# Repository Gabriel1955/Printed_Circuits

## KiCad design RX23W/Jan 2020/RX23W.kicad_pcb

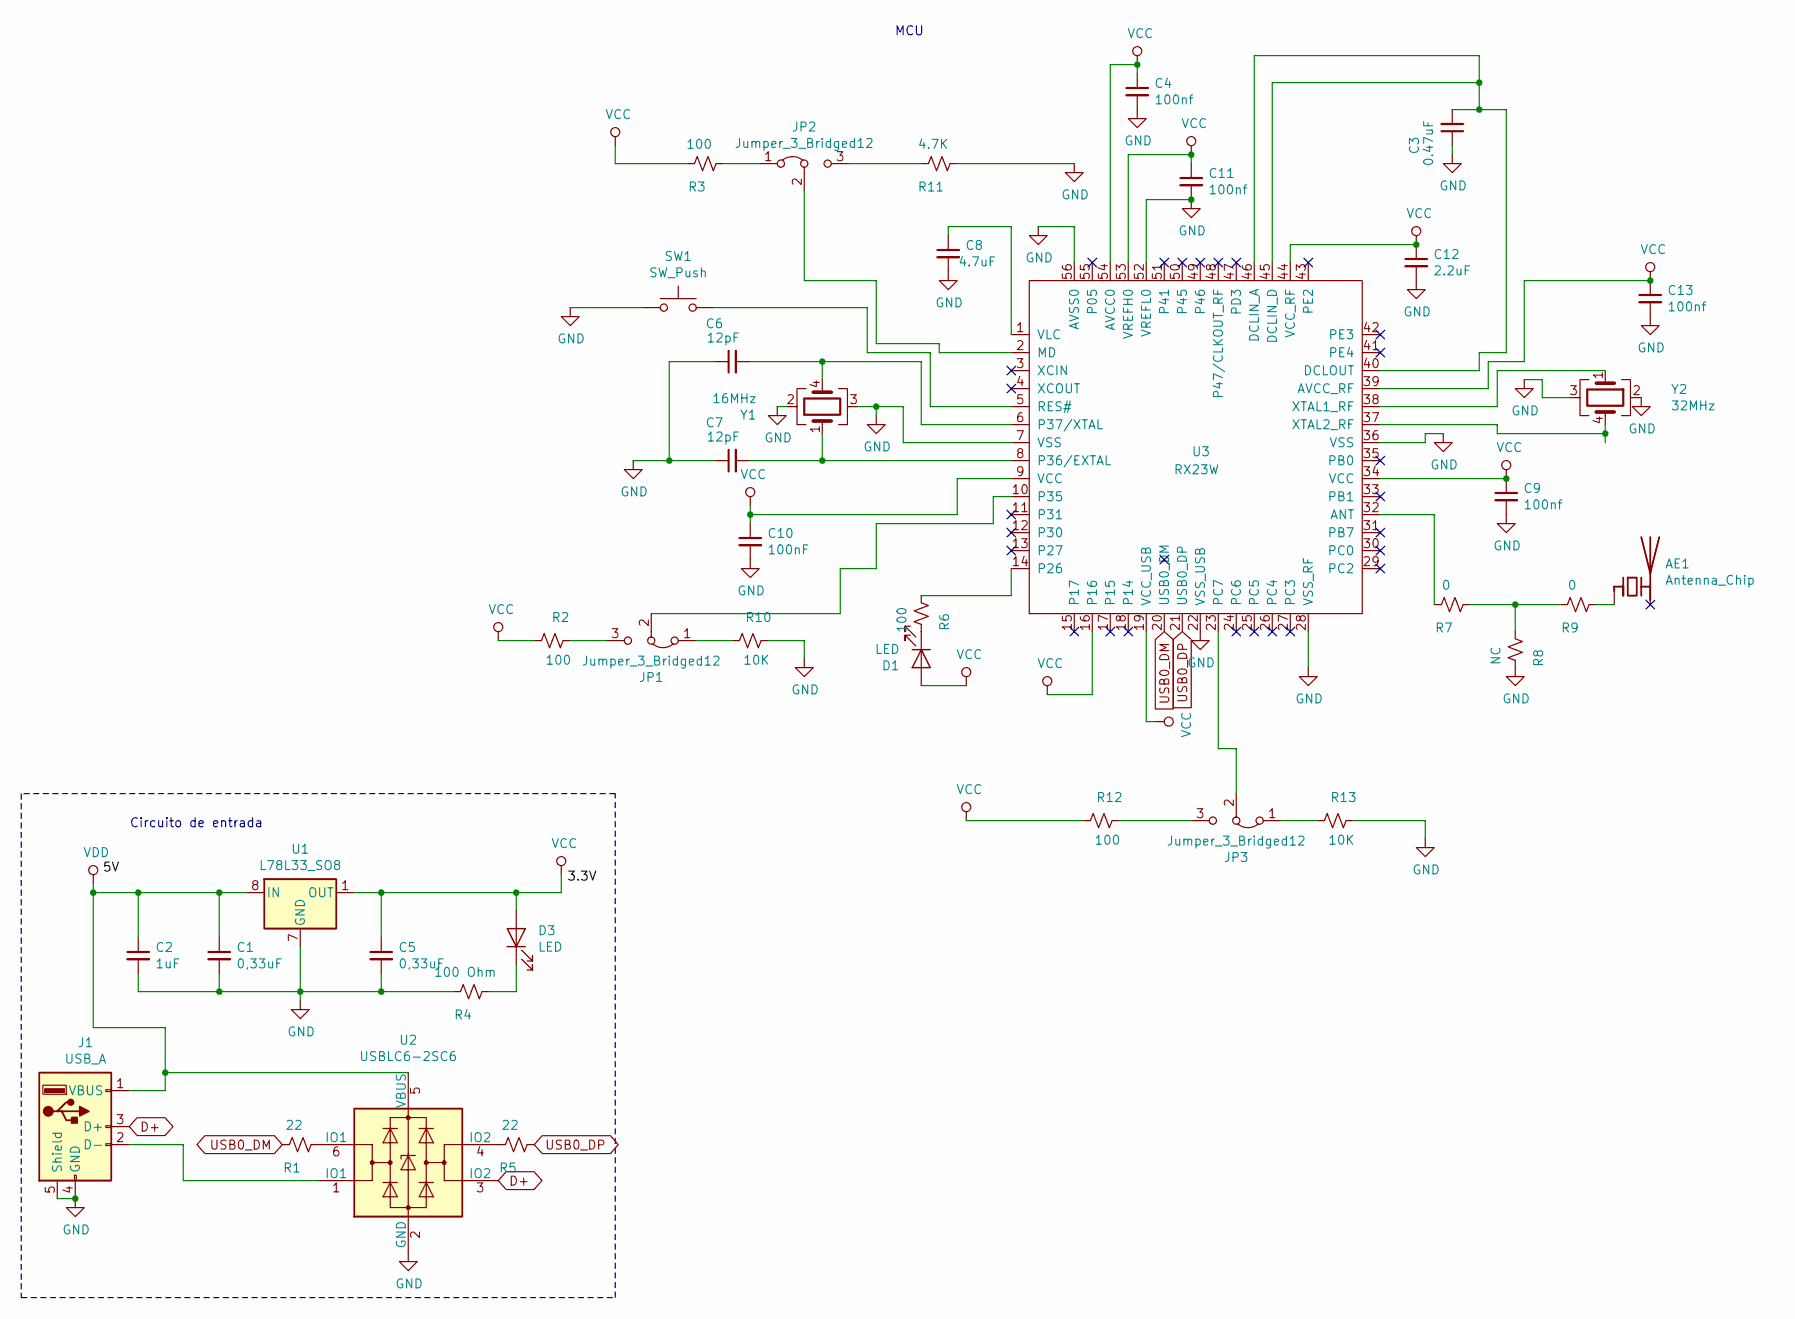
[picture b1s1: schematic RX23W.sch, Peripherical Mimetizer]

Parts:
AE1: Antenna_Chip; XCVR_2450AT42B100E
C1, C5: 0,33uF; C_0402_1005Metric
C2: 1uF; C_0402_1005Metric
C3: 0.47uF; C_0603_1608Metric
C4, C9, C11, C13: 100nf; C_0402_1005Metric
C6, C7: 12pF; C_0402_1005Metric
C8: 4.7uF; C_0402_1005Metric
C10: 100nF; C_0402_1005Metric
C12: 2.2uF; C_0402_1005Metric
D1, D3: LED; LED_0603_1608Metric
J1: USB_A; CUI_UJ2-AV-1-SMT
JP1, JP2, JP3: Jumper_3_Bridged12; SW_SPDT_PCM12
R1, R5: 22; R_0402_1005Metric
R2, R3, R6, R12: 100; R_0402_1005Metric
R4: 100 Ohm; R_0402_1005Metric
R7, R9: 0; R_0402_1005Metric
R8: NC; R_0402_1005Metric
R10, R13: 10K; R_0402_1005Metric
R11: 4.7K; R_0402_1005Metric
SW1: SW_Push; SW_DIP_SPSTx01_Slide_Copal_CHS-01A_W5.08mm_P1.27mm_JPin
U1: L78L33_SO8; SOIC-8_3.9x4.9mm_P1.27mm
U2: USBLC6-2SC6; SOT-23-6
U3: RX23W; QFN-56-1EP_7x7mm_P0.4mm_EP5.6x4.6mm_ThermalVias
Y1: 16MHz; Crystal_SMD_2016_2-4Pin_2.0x1.6mm
Y2: 32MHz; Crystal_SMD_2016_2-4Pin_2.0x1.6mm

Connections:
D+: J1.3 (D+), U2.3 (IO2)
GND: C1.2, C2.2, C3.1, C4.2, C5.2, C6.1, C7.1, C8.2, C9.2, C10.2, C11.2, C12.2, C13.2, J1.4 (GND), J1.5 (Shield), R4.1, R8.1, R10.1, R11.2, R13.1, SW1.1, U1.2 (GND), U1.3 (GND), U1.6 (GND), U1.7 (GND), U2.2 (GND), U3.7 (VSS), U3.22 (VSS_USB), U3.28 (VSS_RF), U3.36 (VSS), U3.52 (VREFL0), U3.56 (AVSS0), Y1.2, Y1.3, Y2.2, Y2.3
unnamed: AE1.1 (FEED), R9.2
unnamed: C3.2, U3.40 (DCLOUT), U3.45 (DCLIN_D), U3.46 (DCLIN_A)
unnamed: C6.2, U3.6 (P37/XTAL), Y1.4
unnamed: C7.2, U3.8 (P36/EXTAL), Y1.1
unnamed: C8.1, U3.1 (VLC)
unnamed: D1.1 (K), R6.1
unnamed: D3.1 (K), R4.2
unnamed: J1.2 (D-), U2.1 (IO1)
unnamed: JP1.1 (A), R10.2
unnamed: JP1.2 (C), U3.10 (P35)
unnamed: JP1.3 (B), R2.1
unnamed: JP2.1 (A), R3.2
unnamed: JP2.2 (C), U3.2 (MD)
unnamed: JP2.3 (B), R11.1
unnamed: JP3.1 (A), R13.2
unnamed: JP3.2 (C), U3.23 (PC7)
unnamed: JP3.3 (B), R12.1
unnamed: R1.2, U2.6 (IO1)
unnamed: R5.1, U2.4 (IO2)
unnamed: R6.2, U3.14 (P26)
unnamed: R7.1, U3.32 (ANT)
unnamed: R7.2, R8.2, R9.1
unnamed: SW1.2, U3.5 (RES#)
unnamed: U3.37 (XTAL2_RF), Y2.4
unnamed: U3.38 (XTAL1_RF), Y2.1
USB0_DM: R1.1, U3.20 (USB0_DM)
USB0_DP: R5.2, U3.21 (USB0_DP)
VCC: C4.1, C5.1, C9.1, C10.1, C11.1, C12.1, C13.1, D1.2 (A), D3.2 (A), R2.2, R3.1, R12.2, U1.1 (OUT), U3.9 (VCC), U3.16, U3.19 (VCC_USB), U3.34 (VCC), U3.39 (AVCC_RF), U3.44 (VCC_RF), U3.53 (VREFH0), U3.54 (AVCC0)
VDD: C1.1, C2.1, J1.1 (VBUS), U1.8 (IN), U2.5 (VBUS)

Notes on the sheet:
Circuito de entrada
MCU

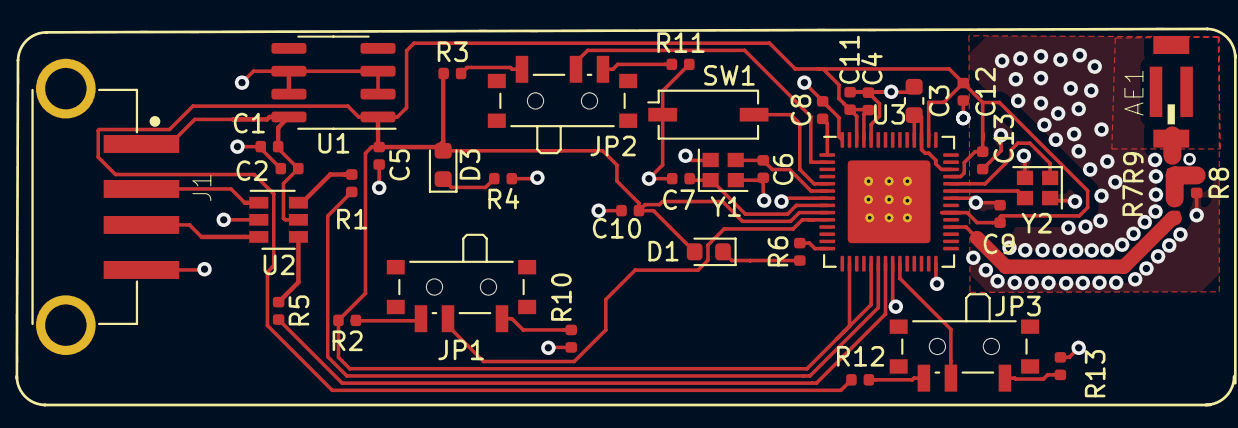
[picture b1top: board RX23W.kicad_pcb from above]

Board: 2 copper layers, 39 parts (0 on the bottom side), 31 nets.

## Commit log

2020-01-31 fishing squematic
2020-01-31 finishing squematic
2020-01-31 squematic
2020-02-14 PCB 0.2
